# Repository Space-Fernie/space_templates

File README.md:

# cubesat_pcb_templates
KiCad templates for Space Concordia's EDA needs

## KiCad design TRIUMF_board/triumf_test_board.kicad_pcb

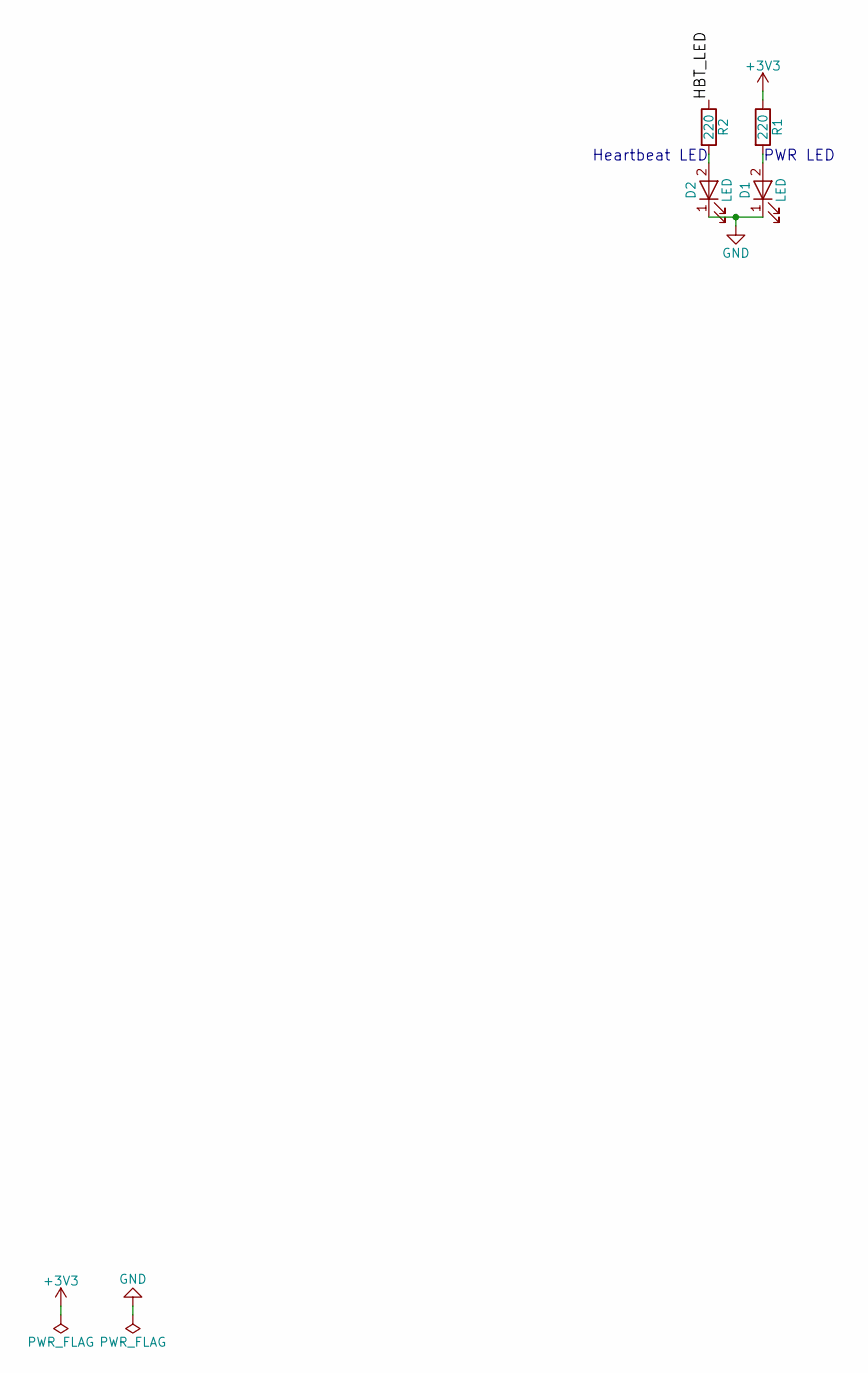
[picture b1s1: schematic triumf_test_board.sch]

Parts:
D1, D2: LED; D_0805
R1, R2: 220; R_0805_HandSoldering

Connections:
+3V3: R1.1
/HBT_LED: R2.1
GND: D1.1 (K), D2.1 (K)
unnamed: D1.2 (A), R1.2
unnamed: D2.2 (A), R2.2

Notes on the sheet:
PWR LED
Heartbeat LED

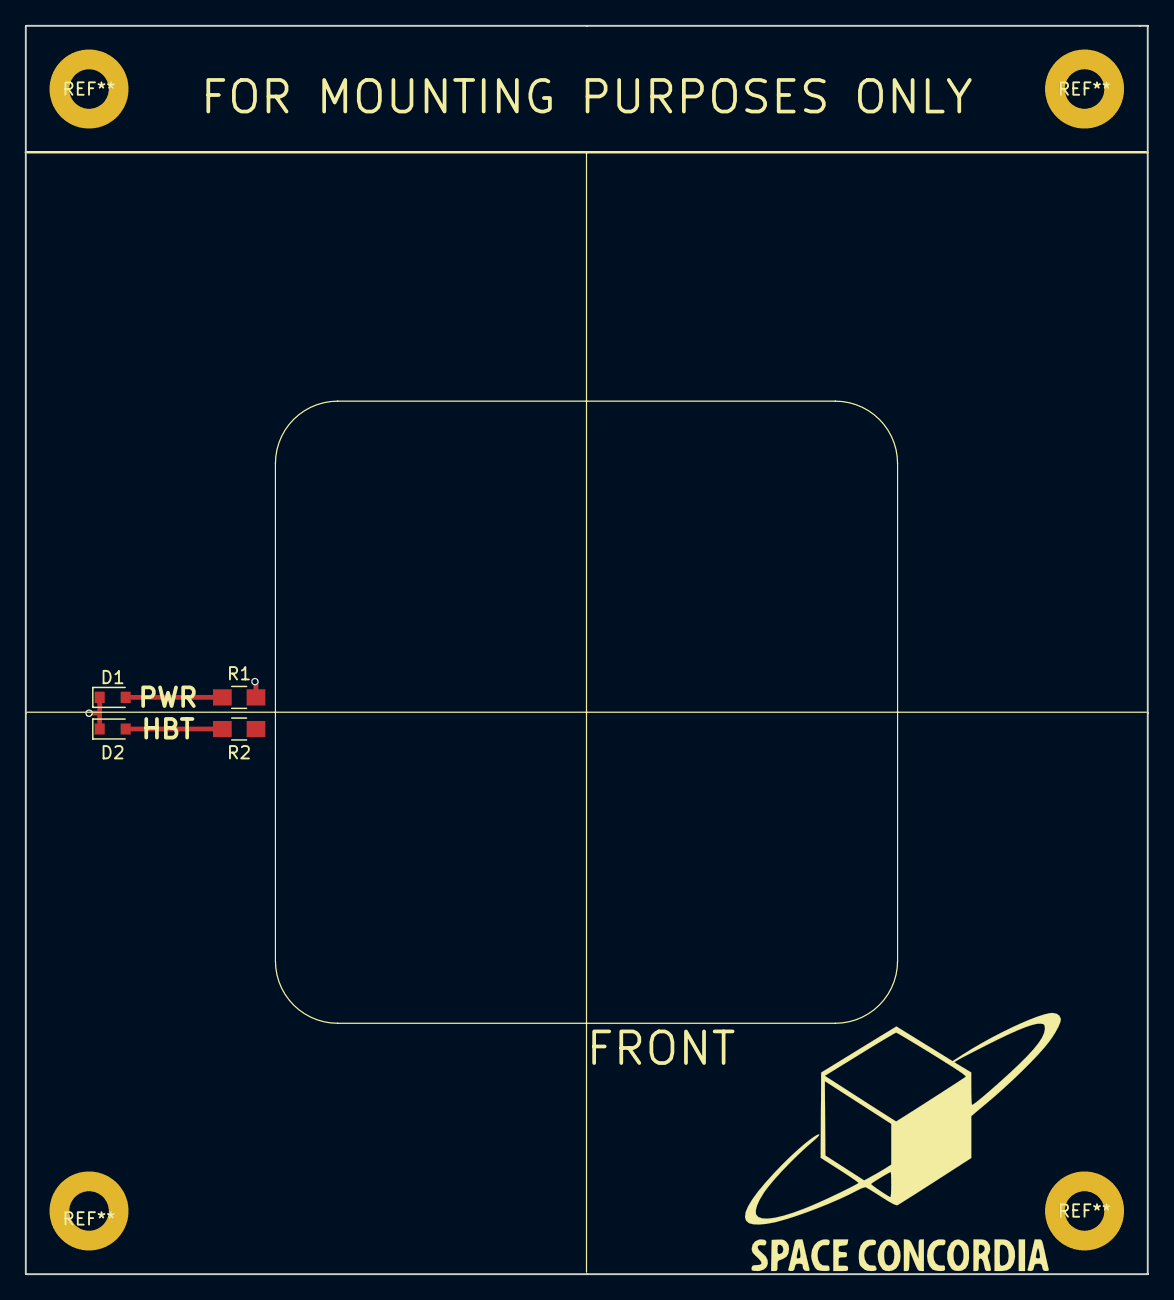
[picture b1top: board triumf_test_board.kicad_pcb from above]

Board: 4 copper layers, 90.2 x 100.3 mm, 4 parts (0 on the bottom side), 3 nets.

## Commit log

2017-10-15 Created icon; created draft paper model; created pcb outline; added 104-connector
2017-10-15 Forgot to previously saver files, slight update
2017-10-20 New dxf without the slot behind the connector, updated board outline to new dxf and marked center of board as center of grids
2017-10-24 Rename kicad_layout_template.kicad_wks to space_kicad_layout_template.kicad_wks
2017-10-26 Created new cubesat board outline, and created draft and step model to be used for vibes analysis
2017-10-28 Defined cubesat board to be 3.6" a side.
2017-10-28 Changed dimensions of the board to accommodate a wider spacing between the mounting holes and the PCB borders. Decreased width of wire slots. Re-created PCB template
2017-10-29 Updated step file, started defining holes for the drafting
2017-10-31 Changed pcb outline template to be based off of eagle board schematics
2017-10-31 Fixed DXF for cubesat board template
2017-11-01 Finalized physical pcb template design, guidelines and rules to follow
2017-11-20 Slight fixes
2017-11-22 Added board for triumf
2018-01-10 Modified mounting holes
2018-01-13 Started defining cubesat bus nets
2018-02-03 Changed some nets
2018-02-18 Updated CubeSat board template
2018-02-23 Replaced MOTOR_CONFIG channels with MOTOR_ENC channels
